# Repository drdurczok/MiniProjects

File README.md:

# MiniProjects
Compilation of small side projects

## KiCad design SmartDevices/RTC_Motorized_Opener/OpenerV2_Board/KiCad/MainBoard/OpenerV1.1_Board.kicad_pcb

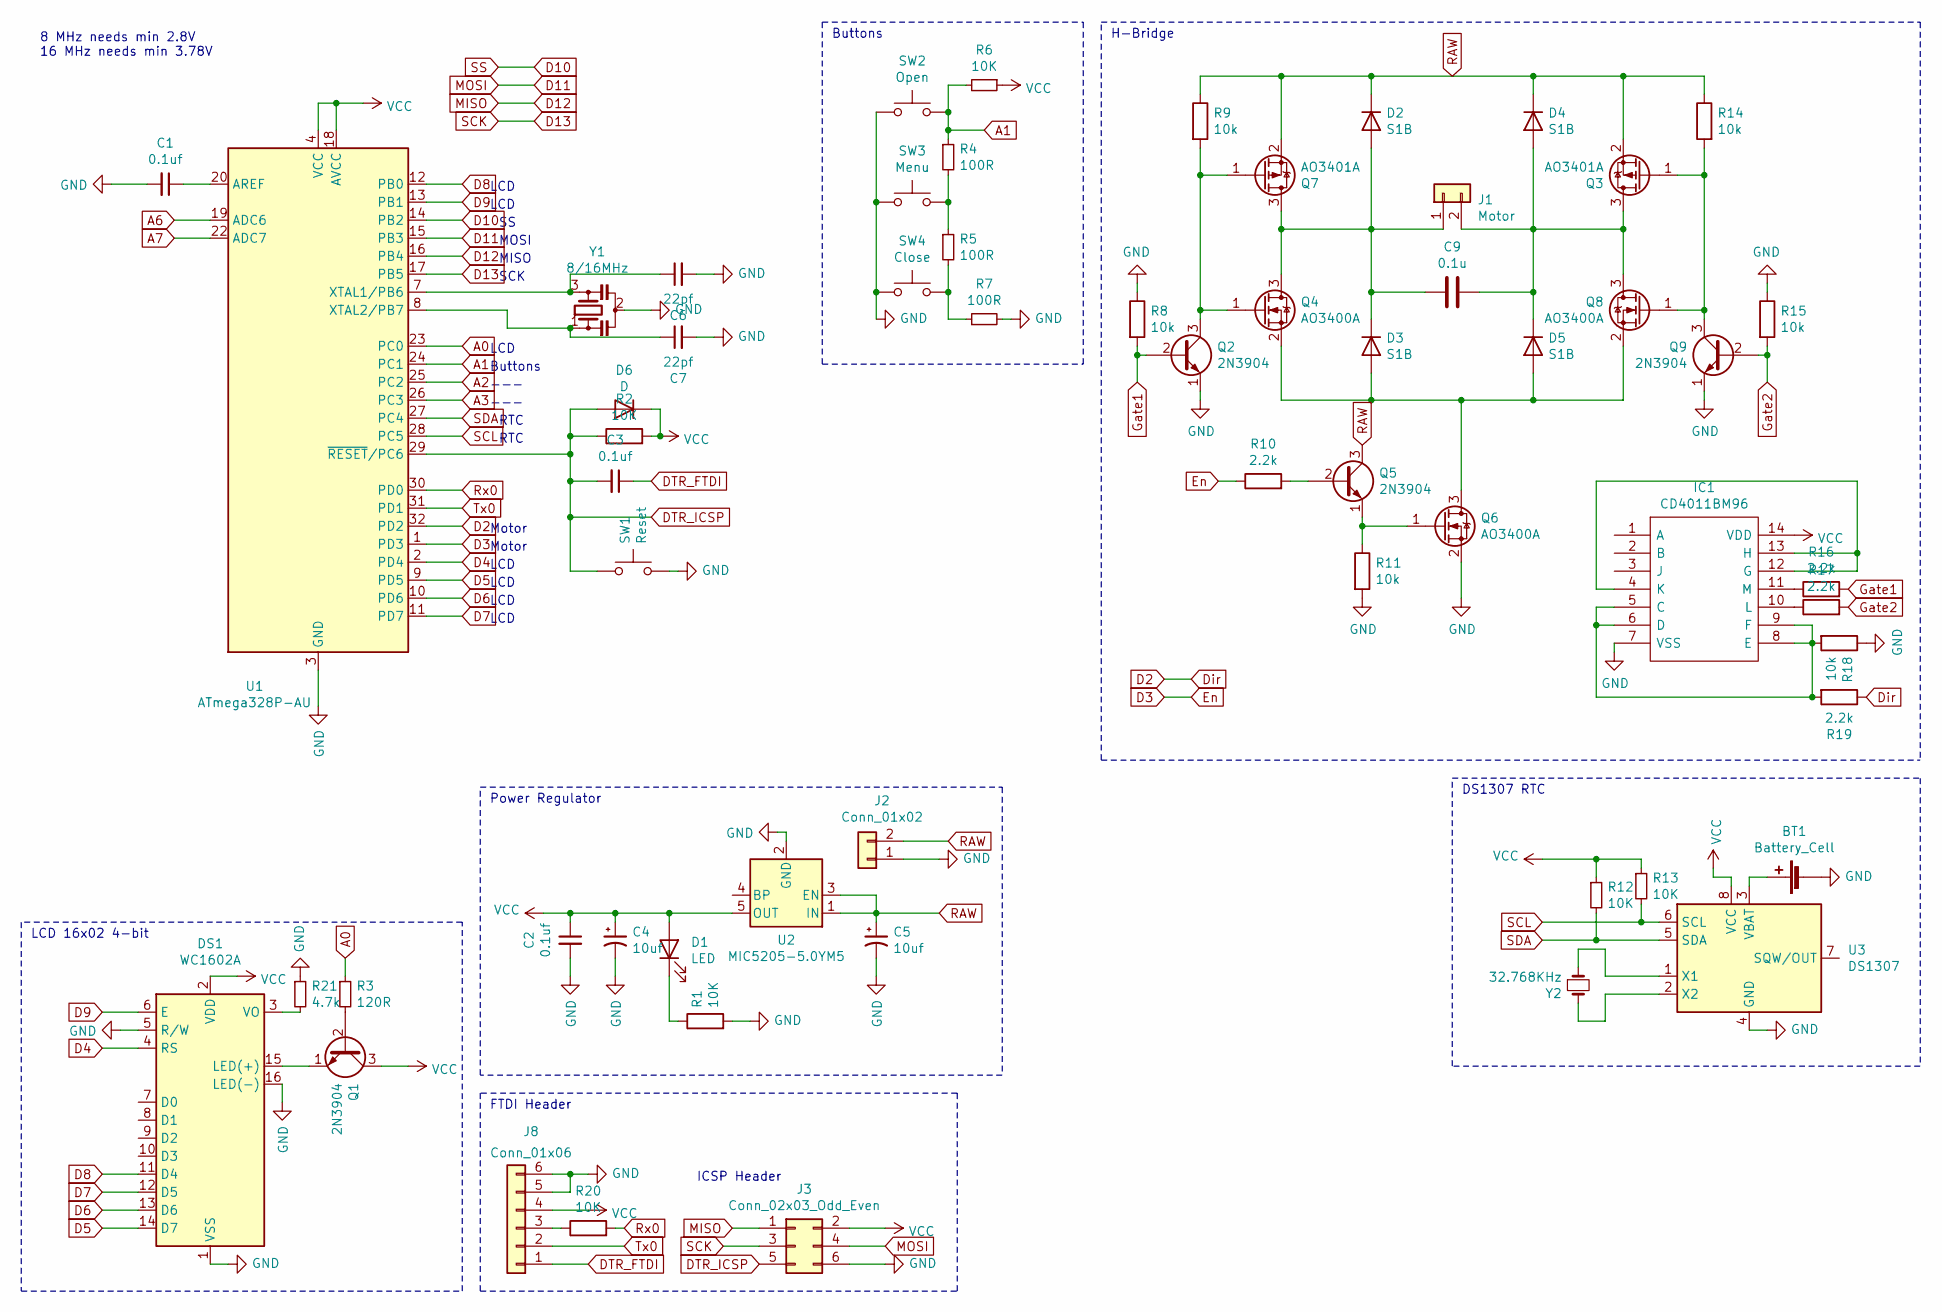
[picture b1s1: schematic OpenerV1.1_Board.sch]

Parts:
BT1: Battery_Cell; BatteryHolder_Keystone_103_1x20mm
C1, C2, C3: 0.1uf; C_1210_3225Metric
C4, C5: 10uf; CP_EIA-3216-18_Kemet-A
C6, C7: 22pf; C_Disc_D5.0mm_W2.5mm_P2.50mm
C9: 0.1u; C_1210_3225Metric
D1: LED; LED_0805_2012Metric
D2, D3, D4, D5: S1B; D_SMA
D6: D; D_SMA
DS1: WC1602A
IC1: CD4011BM96; SOIC127P600X175-14N; Manufacturer_Part_Number CD4011BM96; Mouser Part Number 595-CD4011BM96
J1: Motor; PinHeader_1x02_P2.54mm_Vertical
J2: Conn_01x02; PinHeader_1x02_P2.54mm_Vertical
J3: Conn_02x03_Odd_Even; PinHeader_2x03_P2.54mm_Vertical
J8: Conn_01x06; PinHeader_1x06_P2.54mm_Vertical
Q1, Q2, Q5, Q9: 2N3904; TO-92_Inline_Wide
Q3, Q7: AO3401A; SOT-23
Q4, Q6, Q8: AO3400A; SOT-23
R1, R2, R6, R12, R13, R20: 10K; R_0805_2012Metric
R3: 120R; R_0805_2012Metric
R4, R5, R7: 100R; R_0805_2012Metric
R8, R9, R11, R14, R15, R18: 10k; R_0805_2012Metric
R10, R16, R17, R19: 2.2k; R_0805_2012Metric
R21: 4.7k; R_0805_2012Metric
SW1: Reset; SW_PUSH_6mm_H5mm
SW2: Open; SW_PUSH_6mm_H5mm
SW3: Menu; SW_PUSH_6mm_H5mm
SW4: Close; SW_PUSH_6mm_H5mm
U1: ATmega328P-AU; TQFP-32_7x7mm_P0.8mm
U2: MIC5205-5.0YM5; SOT-23-5
U3: DS1307; SOIC-8_3.9x4.9mm_P1.27mm
Y1: 8/16MHz; Resonator-3Pin_W10.0mm_H5.0mm
Y2: 32.768KHz; Crystal_HC18-U_Vertical

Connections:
A0: R3.1, U1.23 (PC0)
A1: R4.1, R6.2, SW2.2, U1.24 (PC1)
A2: U1.25 (PC2)
A3: U1.26 (PC3)
A6: U1.19 (ADC6)
A7: U1.22 (ADC7)
D2: R19.1, U1.32 (PD2)
D3: R10.1, U1.1 (PD3)
D4: DS1.4 (RS), U1.2 (PD4)
D5: DS1.14 (D7), U1.9 (PD5)
D6: DS1.13 (D6), U1.10 (PD6)
D7: DS1.12 (D5), U1.11 (PD7)
D8: DS1.11 (D4), U1.12 (PB0)
D9: DS1.6 (E), U1.13 (PB1)
D10: U1.14 (PB2)
D11: J3.4, U1.15 (PB3)
D12: J3.1, U1.16 (PB4)
D13: J3.3, U1.17 (PB5)
DTR_FTDI: C3.1, J8.1
DTR_ICSP: C3.2, D6.2 (A), J3.5, R2.1, SW1.1, U1.29 (~RESET~/PC6)
GND: BT1.2 (-), C1.2, C2.2, C4.2, C5.2, C6.2, C7.2, DS1.1 (VSS), DS1.5 (R/W), DS1.16 (LED(-)), IC1.7 (VSS), J2.1, J3.6, J8.5, J8.6, Q2.1 (E), Q6.2 (S), Q9.1 (E), R1.2, R7.2, R8.1, R11.2, R15.1, R18.1, R21.1, SW1.2, SW2.1, SW3.1, SW4.1, U1.3 (GND), U1.5 (GND), U1.21 (GND), U2.2 (GND), U3.4 (GND), Y1.2
Gate1: Q2.2 (B), R8.2, R16.2
Gate2: Q9.2 (B), R15.2, R17.2
unnamed: BT1.1 (+), U3.3 (VBAT)
unnamed: C1.1, U1.20 (AREF)
unnamed: C6.1, U1.7 (XTAL1/PB6), Y1.3
unnamed: C7.1, U1.8 (XTAL2/PB7), Y1.1
unnamed: C9.1, D4.2 (A), D5.1 (K), J1.2, Q3.3 (D), Q8.3 (D)
unnamed: C9.2, D2.2 (A), D3.1 (K), J1.1, Q4.3 (D), Q7.3 (D)
unnamed: D1.1 (K), R1.1
unnamed: D3.2 (A), D5.2 (A), Q4.2 (S), Q6.3 (D), Q8.2 (S)
unnamed: DS1.3 (VO), R21.2
unnamed: DS1.15 (LED(+)), Q1.1 (E)
unnamed: IC1.5 (C), IC1.6 (D), IC1.8 (E), IC1.9 (F), R18.2, R19.2
unnamed: IC1.10 (L), R17.1
unnamed: IC1.11 (M), R16.1
unnamed: IC1.4 (K), IC1.12 (G), IC1.13 (H)
unnamed: J8.3, R20.1
unnamed: Q1.2 (B), R3.2
unnamed: Q2.3 (C), Q4.1 (G), Q7.1 (G), R9.2
unnamed: Q3.1 (G), Q8.1 (G), Q9.3 (C), R14.2
unnamed: Q5.1 (E), Q6.1 (G), R11.1
unnamed: Q5.2 (B), R10.2
unnamed: R4.2, R5.1, SW3.2
unnamed: R5.2, R7.1, SW4.2
unnamed: U3.1 (X1), Y2.1
unnamed: U3.2 (X2), Y2.2
RAW: C5.1, D2.1 (K), D4.1 (K), J2.2, Q3.2 (S), Q5.3 (C), Q7.2 (S), R9.1, R14.1, U2.1 (IN), U2.3 (EN)
Rx0: R20.2, U1.30 (PD0)
SCL: R13.2, U1.28 (PC5), U3.6 (SCL)
SDA: R12.2, U1.27 (PC4), U3.5 (SDA)
Tx0: J8.2, U1.31 (PD1)
VCC: C2.1, C4.1, D1.2 (A), D6.1 (K), DS1.2 (VDD), IC1.14 (VDD), J3.2, J8.4, Q1.3 (C), R2.2, R6.1, R12.1, R13.1, U1.4 (VCC), U1.6 (VCC), U1.18 (AVCC), U2.5 (OUT), U3.8 (VCC)

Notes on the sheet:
8 MHz needs min 2.8V 16 MHz needs min 3.78V
Power Regulator
FTDI Header
LCD
MOSI
LCD 16x02 4-bit
MISO
SCK
RTC
DS1307 RTC
Motor
---
H-Bridge
Buttons
ICSP Header

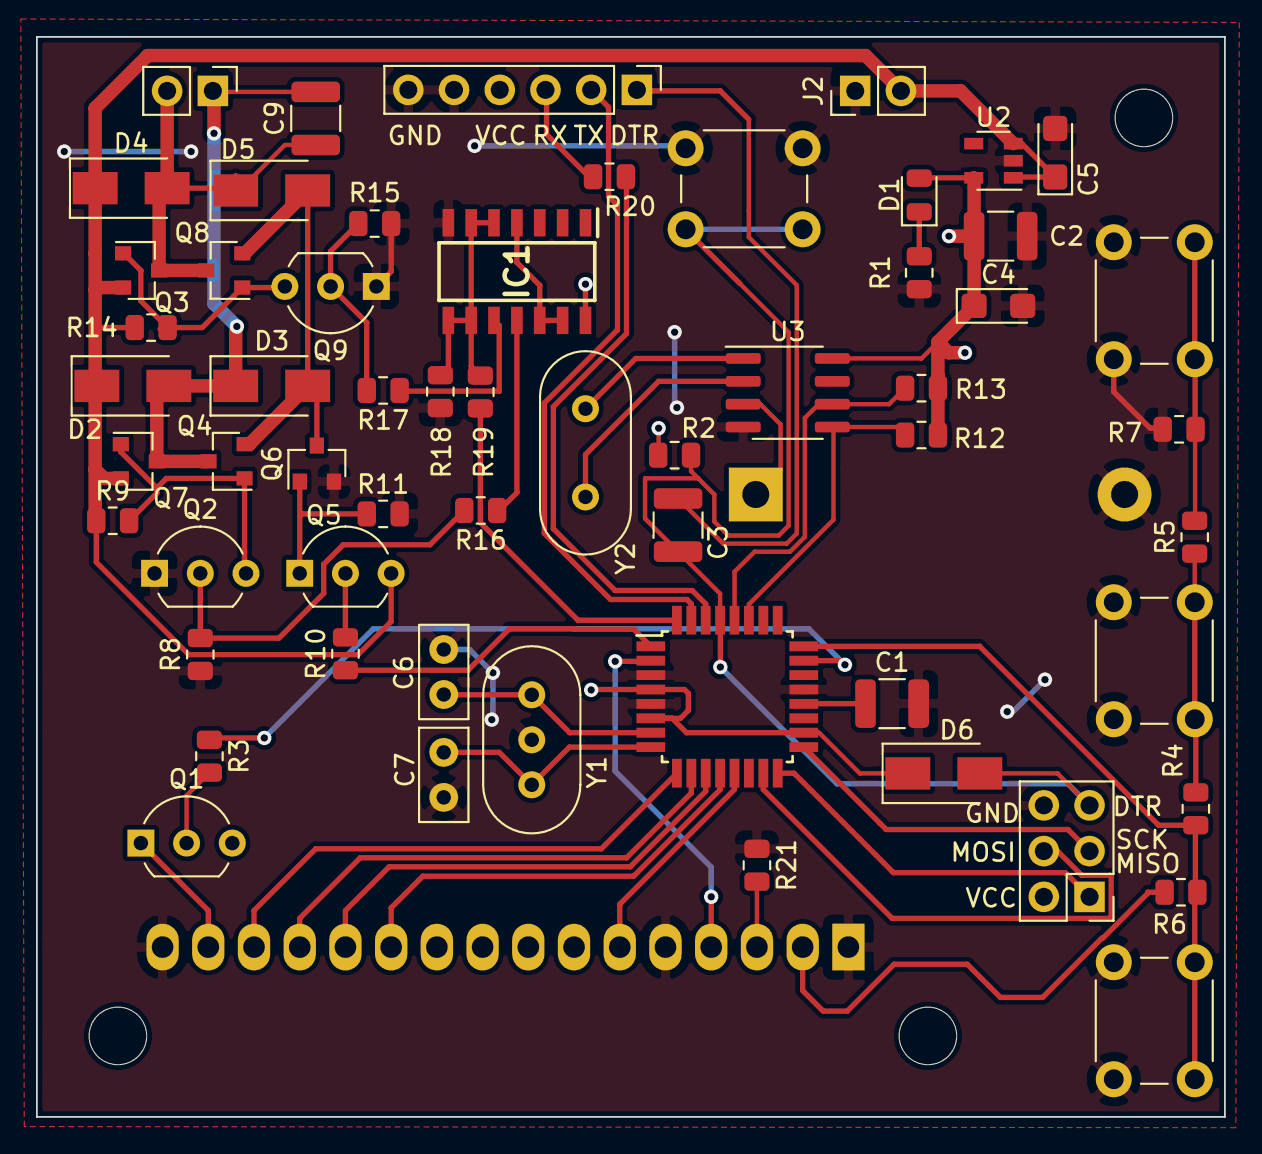
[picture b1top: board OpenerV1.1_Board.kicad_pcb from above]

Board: 2 copper layers, 66.0 x 60.0 mm, 60 parts (1 on the bottom side), 48 nets.

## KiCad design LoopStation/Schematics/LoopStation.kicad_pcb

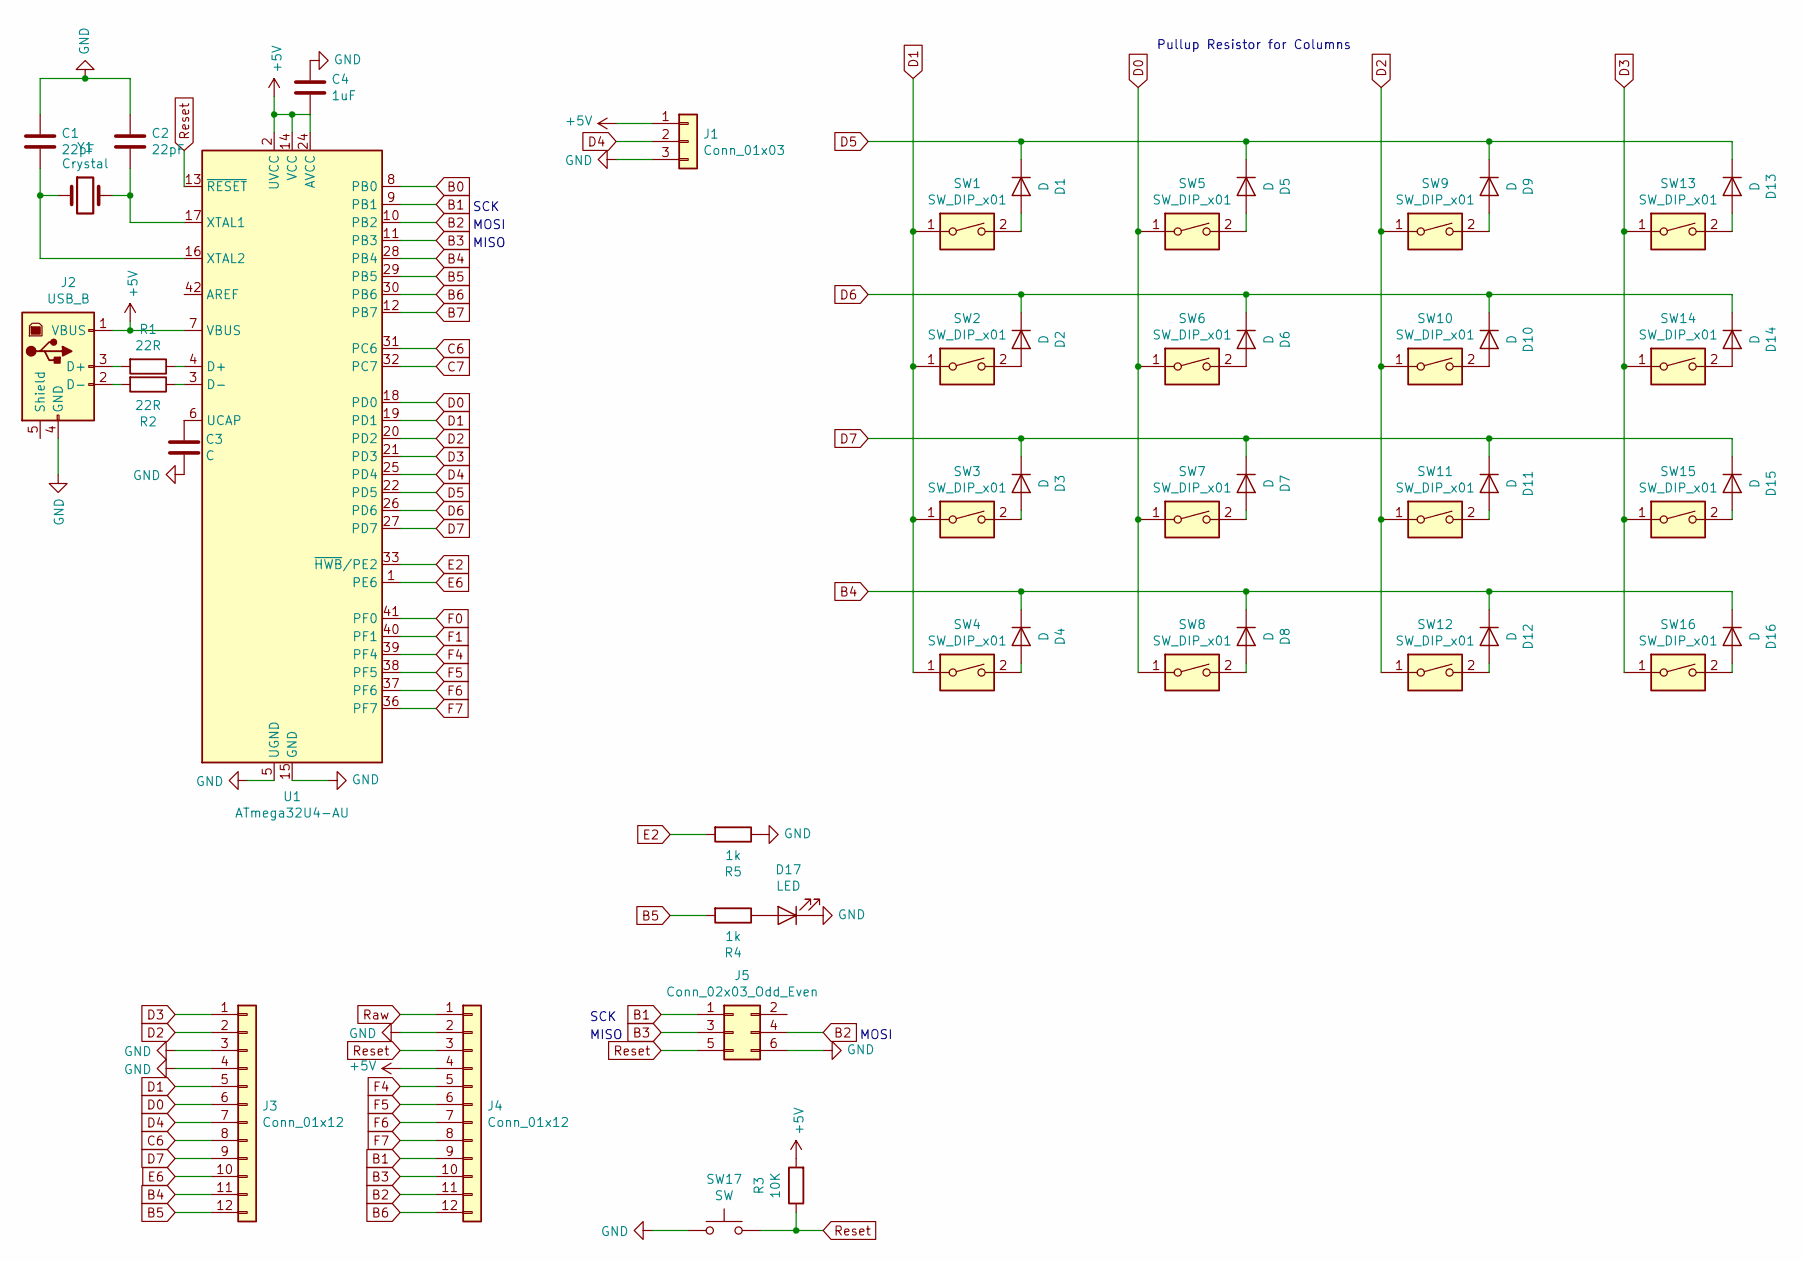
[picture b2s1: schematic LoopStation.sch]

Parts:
C1, C2: 22pF; C_Disc_D9.0mm_W5.0mm_P5.00mm
C3: C; C_Disc_D9.0mm_W5.0mm_P5.00mm
C4: 1uF; C_Disc_D9.0mm_W5.0mm_P5.00mm
D1, D2, D3, D4, D5, D6, D7, D8, D9, D10, D11, D12, D13, D14, D15, D16: D; D_A-405_P10.16mm_Horizontal
D17: LED; LED_D3.0mm
J1: Conn_01x03; PinHeader_1x03_P2.54mm_Vertical
J2: USB_B; USB_B_OST_USB-B1HSxx_Horizontal
J3, J4: Conn_01x12; PinHeader_1x12_P2.54mm_Vertical
J5: Conn_02x03_Odd_Even; PinHeader_2x03_P2.54mm_Vertical
R1, R2: 22R; R_Axial_DIN0207_L6.3mm_D2.5mm_P10.16mm_Horizontal
R3: 10K; R_Axial_DIN0207_L6.3mm_D2.5mm_P10.16mm_Horizontal
R4, R5: 1k; R_Axial_DIN0207_L6.3mm_D2.5mm_P10.16mm_Horizontal
SW1, SW2, SW3, SW4, SW5, SW6, SW7, SW8, SW9, SW10, SW11, SW12, SW13, SW14, SW15, SW16: SW_DIP_x01; SW_PUSH-12mm
SW17: SW; SW_PUSH_6mm
U1: ATmega32U4-AU; TQFP-44_10x10mm_P0.8mm
Y1: Crystal; Crystal_HC18-U_Vertical

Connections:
+5V: C4.2, J1.1, J2.1 (VBUS), J4.4, R3.2, U1.2 (UVCC), U1.7 (VBUS), U1.14 (VCC), U1.24 (AVCC), U1.34 (VCC), U1.44 (AVCC)
B0: U1.8 (PB0)
B1: J4.9, J5.1, U1.9 (PB1)
B2: J4.11, J5.4, U1.10 (PB2)
B3: J4.10, J5.3, U1.11 (PB3)
B4: D4.1 (K), D8.1 (K), D12.1 (K), D16.1 (K), J3.11, U1.28 (PB4)
B5: J3.12, R4.2, U1.29 (PB5)
B6: J4.12, U1.30 (PB6)
B7: U1.12 (PB7)
C6: J3.8, U1.31 (PC6)
C7: U1.32 (PC7)
D0: J3.6, SW5.1, SW6.1, SW7.1, SW8.1, U1.18 (PD0)
D1: J3.5, SW1.1, SW2.1, SW3.1, SW4.1, U1.19 (PD1)
D2: J3.2, SW9.1, SW10.1, SW11.1, SW12.1, U1.20 (PD2)
D3: J3.1, SW13.1, SW14.1, SW15.1, SW16.1, U1.21 (PD3)
D4: J1.2, J3.7, U1.25 (PD4)
D5: D1.1 (K), D5.1 (K), D9.1 (K), D13.1 (K), U1.22 (PD5)
D6: D2.1 (K), D6.1 (K), D10.1 (K), D14.1 (K), U1.26 (PD6)
D7: D3.1 (K), D7.1 (K), D11.1 (K), D15.1 (K), J3.9, U1.27 (PD7)
E2: R5.2, U1.33 (~HWB~/PE2)
E6: J3.10, U1.1 (PE6)
F0: U1.41 (PF0)
F1: U1.40 (PF1)
F4: J4.5, U1.39 (PF4)
F5: J4.6, U1.38 (PF5)
F6: J4.7, U1.37 (PF6)
F7: J4.8, U1.36 (PF7)
GND: C1.1, C2.1, C3.2, C4.1, D17.1 (K), J1.3, J2.4 (GND), J3.3, J3.4, J4.2, J5.6, R5.1, SW17.1, U1.5 (UGND), U1.15 (GND), U1.23 (GND), U1.35 (GND), U1.43 (GND)
unnamed: C1.2, U1.16 (XTAL2), Y1.1
unnamed: C2.2, U1.17 (XTAL1), Y1.2
unnamed: C3.1, U1.6 (UCAP)
unnamed: D1.2 (A), SW1.2
unnamed: D2.2 (A), SW2.2
unnamed: D3.2 (A), SW3.2
unnamed: D4.2 (A), SW4.2
unnamed: D5.2 (A), SW5.2
unnamed: D6.2 (A), SW6.2
unnamed: D7.2 (A), SW7.2
unnamed: D8.2 (A), SW8.2
unnamed: D9.2 (A), SW9.2
unnamed: D10.2 (A), SW10.2
unnamed: D11.2 (A), SW11.2
unnamed: D12.2 (A), SW12.2
unnamed: D13.2 (A), SW13.2
unnamed: D14.2 (A), SW14.2
unnamed: D15.2 (A), SW15.2
unnamed: D16.2 (A), SW16.2
unnamed: D17.2 (A), R4.1
unnamed: J2.2 (D-), R2.2
unnamed: J2.3 (D+), R1.2
unnamed: R1.1, U1.4 (D+)
unnamed: R2.1, U1.3 (D-)
Reset: J4.3, J5.5, R3.1, SW17.2, U1.13 (~RESET)

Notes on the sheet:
Pullup Resistor for Columns
MISO
SCK
MOSI

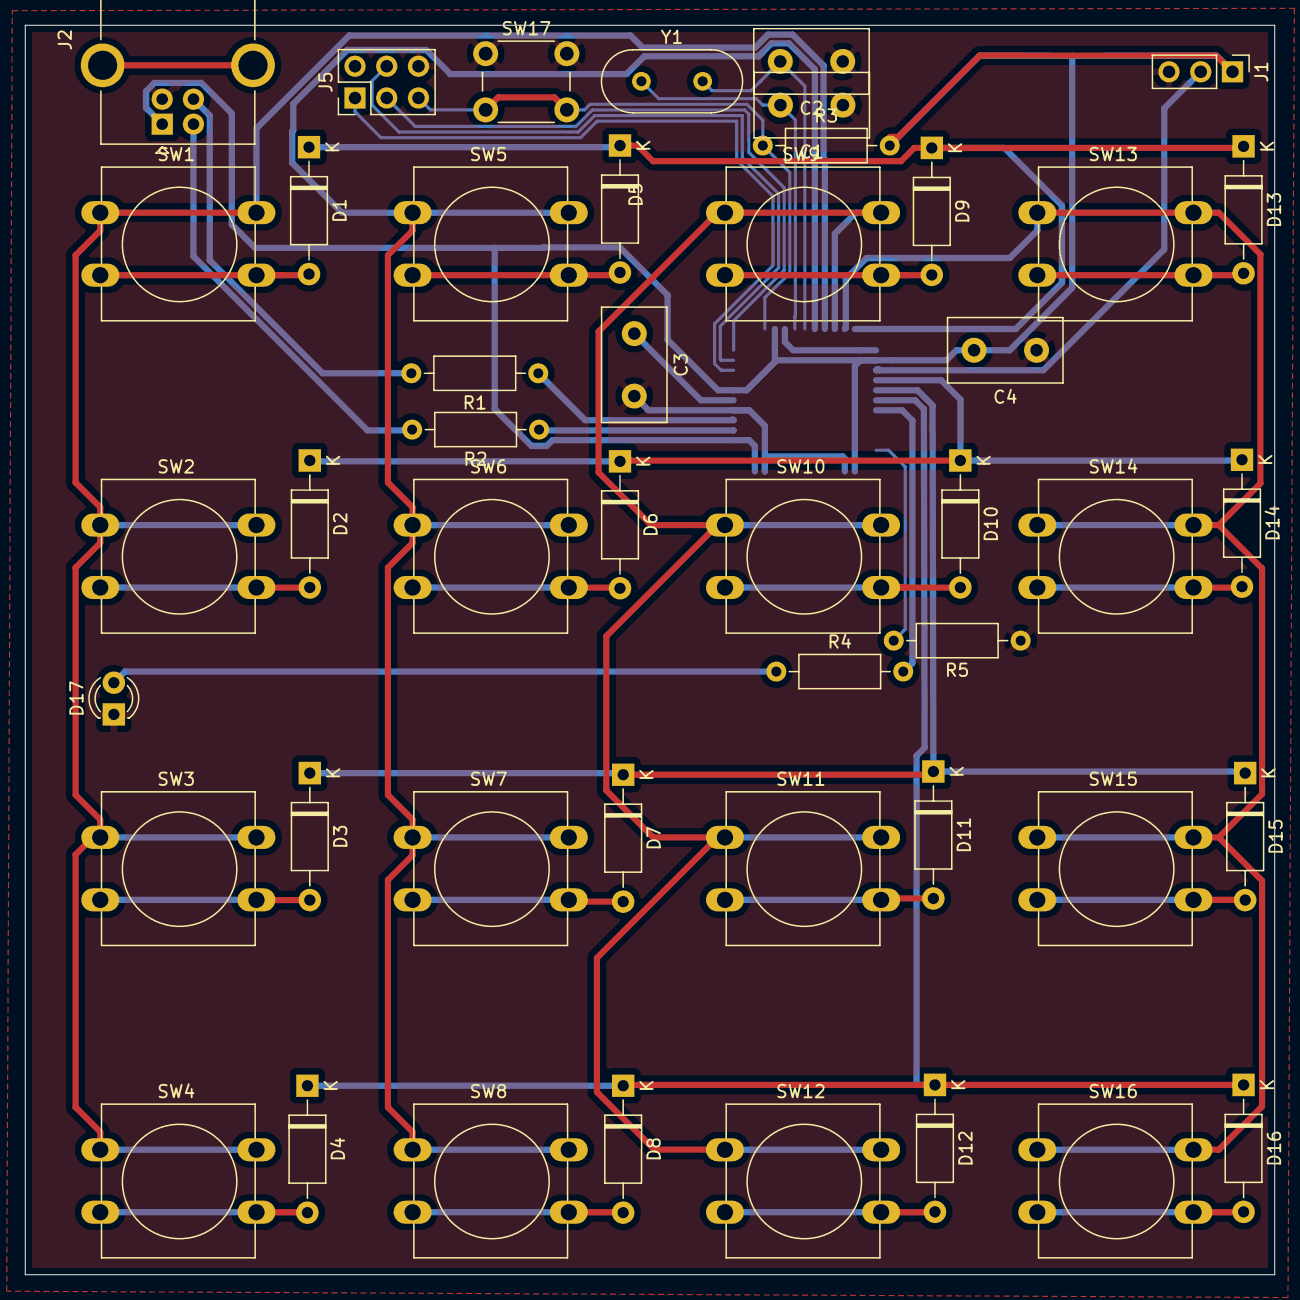
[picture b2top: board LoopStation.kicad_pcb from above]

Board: 2 copper layers, 100.0 x 100.0 mm, 48 parts (1 on the bottom side), 41 nets.

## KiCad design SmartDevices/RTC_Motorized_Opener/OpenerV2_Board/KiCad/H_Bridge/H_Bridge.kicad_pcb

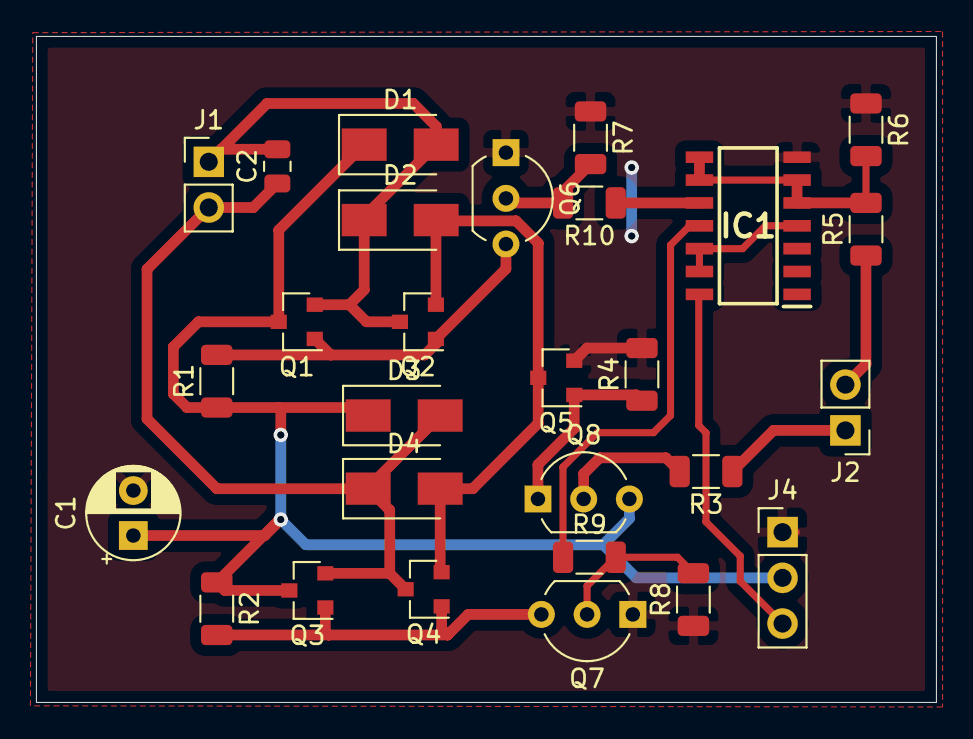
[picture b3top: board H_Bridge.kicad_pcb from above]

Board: 2 copper layers, 50.0 x 37.0 mm, 28 parts (0 on the bottom side), 18 nets.

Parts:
C1: 1000u; CP_Radial_D5.0mm_P2.50mm
C2: 0.1u; C_0805_2012Metric
D1, D2, D3, D4: S1B; D_SMA
IC1: CD4011BM96; SOIC127P600X175-14N
J1, J2: Motor; PinHeader_1x02_P2.54mm_Vertical
J4: Motor; PinHeader_1x03_P2.54mm_Vertical
Q1, Q3: AO3401A; SOT-23
Q2, Q4, Q5: AO3400A; SOT-23
Q6, Q7, Q8: 2N3904; TO-92_Inline_Wide
R1, R2, R4, R6, R7, R8: 10k; R_1206_3216Metric
R3, R5, R9, R10: 2.2k; R_1206_3216Metric

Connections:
+5V: IC1.14, J4.3
+12V: C1.1, D1.1, D3.1, J4.2, Q1.3, Q3.3, Q8.3, R1.1, R2.1
Dir: J2.2, R5.1
En: J2.1, R3.1
GND: C1.2, IC1.7, J4.1, Q5.2, Q6.1, Q7.1, R4.2, R6.1, R7.1, R8.1
Gate1: Q6.2, R7.2, R10.2
Gate2: Q7.2, R8.2, R9.2
unnamed: C2.1, D3.2, D4.1, J1.2, Q3.2, Q4.3
unnamed: C2.2, D1.2, D2.1, J1.1, Q1.2, Q2.3
unnamed: D2.2, D4.2, Q2.2, Q4.2, Q5.3
unnamed: IC1.5, IC1.6, IC1.8, IC1.9, R5.2, R6.2
unnamed: IC1.10, R10.1
unnamed: IC1.11, R9.1
unnamed: IC1.4, IC1.12, IC1.13
unnamed: Q1.1, Q2.1, Q6.3, R1.2
unnamed: Q3.1, Q4.1, Q7.3, R2.2
unnamed: Q5.1, Q8.1, R4.1
unnamed: Q8.2, R3.2

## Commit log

2017-06-04 Version 1.0
2017-06-04 Working
2018-01-25 WaterCooling_Init
2018-02-13 FirstPrototype
2018-02-14 Restructure
2018-02-14 fixed
2018-02-14 subtle changes
2018-02-28 Mechanism PPL
2018-03-03 Reorganization
2018-06-14 Website HTML,PHP,SQL
2021-09-14 Added new miniprojects
2021-09-15 Loopstation added WS2812B control and improved button grid
2021-12-31 Opener Project added
2021-12-31 Updated loopstation arduino code
2021-12-31 Opener RTC library added
2022-01-03 PM arduino library added
2022-01-03 Updated Loopstation CAD
2022-01-03 Replaced PM library
2022-01-03 Added UTFT library
2022-01-03 Added URTouch library
2022-01-07 Removed Zipped files
2022-01-07 Removed Zip File
2022-01-07 Renamed Folder
2022-01-07 File Restructure
2022-01-07 Fixed TX RX Swapped pins
2022-01-11 CAD model for Opener
2022-01-12 Fixing button bouncing
2022-01-14 PM Sensor Base CAD
2022-01-17 Updated Base for PM Sensor
2022-01-23 Better Button Polling for RTC Motorized Opener
2022-01-24 Removed Calibration Menu
2022-01-24 Minor Value Tweak
2022-01-27 Fixed Transistor Orientation
2022-02-04 Designed new CAD part
